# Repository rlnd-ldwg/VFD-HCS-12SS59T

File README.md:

# Arduino Driver for Samsung HCS-12SS59T VFDisplay
quick and simple schematics, driver and example

## 

## Code
-> source directory

## Schematics
### Display

- for simple DC filament supply  
  connect Vcc to VF+  
  mix normal and schottky diodes on VF- for desired voltage  
  keeping VF low extends tungsten filament lifetime  
  voltages starting with 2.7 V up to 3.6 V are working  
  do not exceed 125 mA!
- -> [AC Filament Supply](#ac-filament-supply) 

### Anode and Grid Supply

- activate Vdisp  
  in VFD.h set `SUPPLYMODE 0`
- the simple _VDON with 1N4148 does not switch off Vdisp entirely,  
  maybe it can be omitted because the 470 ohm resistor on Vdisp  
  restricts current for VFD grid and anode

### AC Filament Supply

- activate Vdisp  https://electronics.stackexchange.com/questions/230044/help-driving-a-vfd-display
  in VFD.h set `SUPPLYMODE 0`
- extended filament endurance  
  (-> google filament notching)
- better brightness distribution  
  (theoretical, can't see any difference to DC supply on this display)
- coil-less

### Combined Clocked Supply

- activate SUCLK_A/B  
  in VFD.h set `SUPPLYMODE 1`

## History
__V0.5__  
initial version  
__V0.6__  
AC filament supply  
__V0.7__  
AC filament supply _VDON  
__V0.8__  
AC filament supply polarity correction  
__V0.9__  
combined clocked supply

## Links
http://www.lapis-semi.com/en/data/datasheet-file_db/display/FEDL9289-01.pdf  
https://www.pollin.de/productdownloads/D121466D.PDF  
https://www.noritake-elec.com/technology/general-technical-information/vfd-operation  
http://www.kerrywong.com/2013/06/05/vfd-filament-driver-using-555/  
https://threeneurons.wordpress.com/vfd-stuff/
https://electronics.stackexchange.com/questions/230044/help-driving-a-vfd-display

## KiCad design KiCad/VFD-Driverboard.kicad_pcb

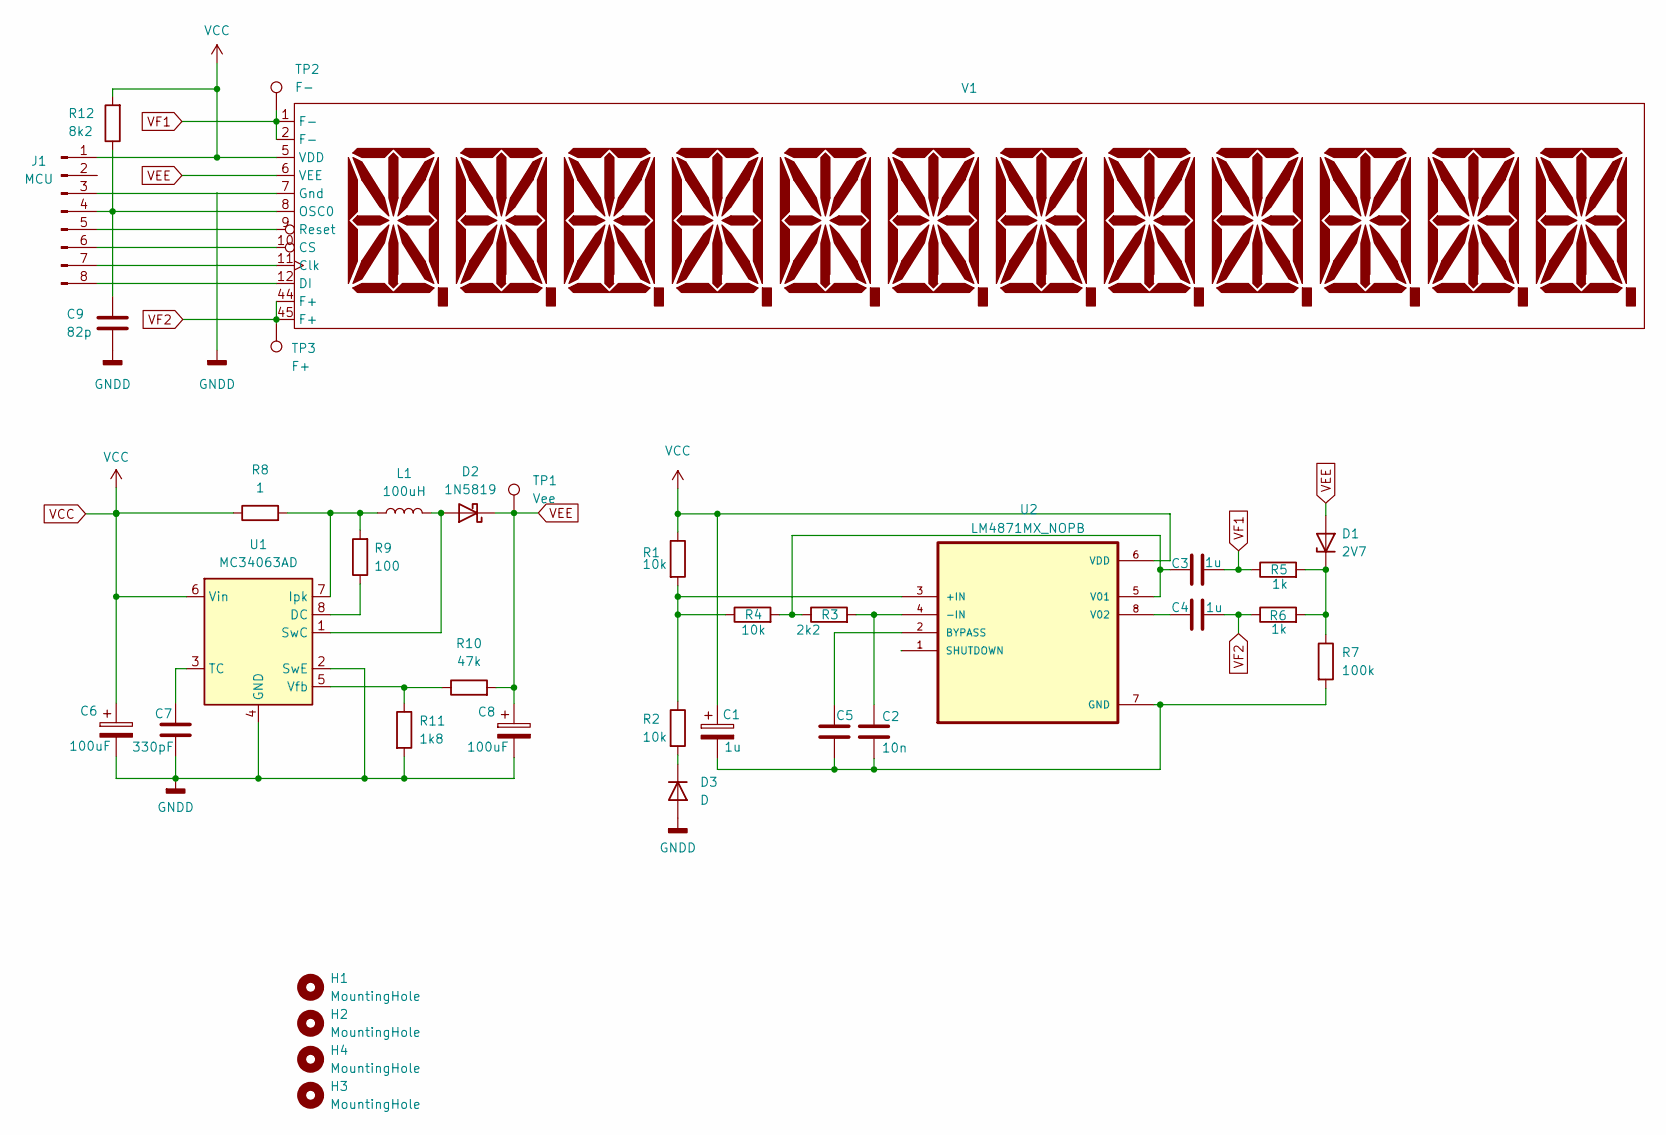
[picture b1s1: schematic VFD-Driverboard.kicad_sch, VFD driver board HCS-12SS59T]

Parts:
C1, C3, C4, C5: 1u; C_2220_5750Metric_Pad1.97x5.40mm_HandSolder
C2: 10n; C_1206_3216Metric_Pad1.33x1.80mm_HandSolder
C6, C8: 100uF; CP_EIA-7343-31_Kemet-D_Pad2.25x2.55mm_HandSolder
C7: 330pF; C_1206_3216Metric_Pad1.33x1.80mm_HandSolder
C9: 82p; C_1206_3216Metric_Pad1.33x1.80mm_HandSolder
D1: 2V7; D_2010_5025Metric_Pad1.52x2.65mm_HandSolder
D2: 1N5819; D_SOD-123
D3: D; D_2010_5025Metric_Pad1.52x2.65mm_HandSolder
H1, H2, H3, H4: MountingHole; MountingHole_3.2mm_M3_ISO14580_Pad_TopBottom
J1: MCU; PinSocket_1x08_P2.54mm_Vertical
L1: 100uH; IND_TAIYO_NRS8040_TAY
R1, R2, R4: 10k; R_1206_3216Metric_Pad1.30x1.75mm_HandSolder
R3: 2k2; R_1206_3216Metric_Pad1.30x1.75mm_HandSolder
R5, R6: 1k; R_1206_3216Metric_Pad1.30x1.75mm_HandSolder
R7: 100k; R_1206_3216Metric_Pad1.30x1.75mm_HandSolder
R8: 1; R_1206_3216Metric_Pad1.30x1.75mm_HandSolder
R9: 100; R_1206_3216Metric_Pad1.30x1.75mm_HandSolder
R10: 47k; R_1206_3216Metric_Pad1.30x1.75mm_HandSolder
R11: 1k8; R_1206_3216Metric_Pad1.30x1.75mm_HandSolder
R12: 8k2; R_1206_3216Metric_Pad1.30x1.75mm_HandSolder
TP1: Vee; TestPoint_Pad_D2.5mm
TP2: F-; TestPoint_Pad_D2.5mm
TP3: F+; TestPoint_Pad_D2.5mm
U1: MC34063AD; SOIC127P599X175-8N
U2: LM4871MX_NOPB; SOIC127P599X175-8N
V1: VFD HCS-12SS59T

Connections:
unnamed: D1.1 (K), R5.2, R6.2, R7.1
unnamed: D2.2 (A), L1.2, U1.1 (SwC)
unnamed: D3.1 (K), R2.2
unnamed: J1.3, V1.7 (Gnd)
unnamed: C9.2, J1.4, R12.1, V1.8 (OSC0)
unnamed: J1.5, V1.9 (Reset)
unnamed: J1.6, V1.10 (CS)
unnamed: J1.7, V1.11 (Clk)
unnamed: J1.8, V1.12 (DI)
unnamed: R9.1, U1.8 (DC)
unnamed: L1.1, R8.2, R9.2, U1.7 (Ipk)
unnamed: C7.1, U1.3 (TC)
unnamed: R10.1, R11.1, U1.5 (Vfb)
unnamed: R1.2, R2.1, R4.1, U2.3 (+IN)
unnamed: C2.1, R3.2, U2.4 (-IN)
unnamed: C5.1, U2.2 (BYPASS)
unnamed: C1.2, C2.2, C5.2, R7.2, U2.7 (GND)
unnamed: C3.1, R3.1, R4.2, U2.5 (V01)
unnamed: C4.1, U2.8 (V02)
VCC: C1.1, C6.1, J1.1, R1.1, R8.1, R12.2, U1.6 (Vin), U2.6 (VDD), V1.5 (VDD)
VEE: C8.1, D1.2 (A), D2.1 (K), R10.2, TP1.1, V1.6 (VEE)
VF1: C3.2, R5.1, TP2.1, V1.1 (F-), V1.2 (F-)
VF2: C4.2, R6.1, TP3.1, V1.44 (F+), V1.45 (F+)

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
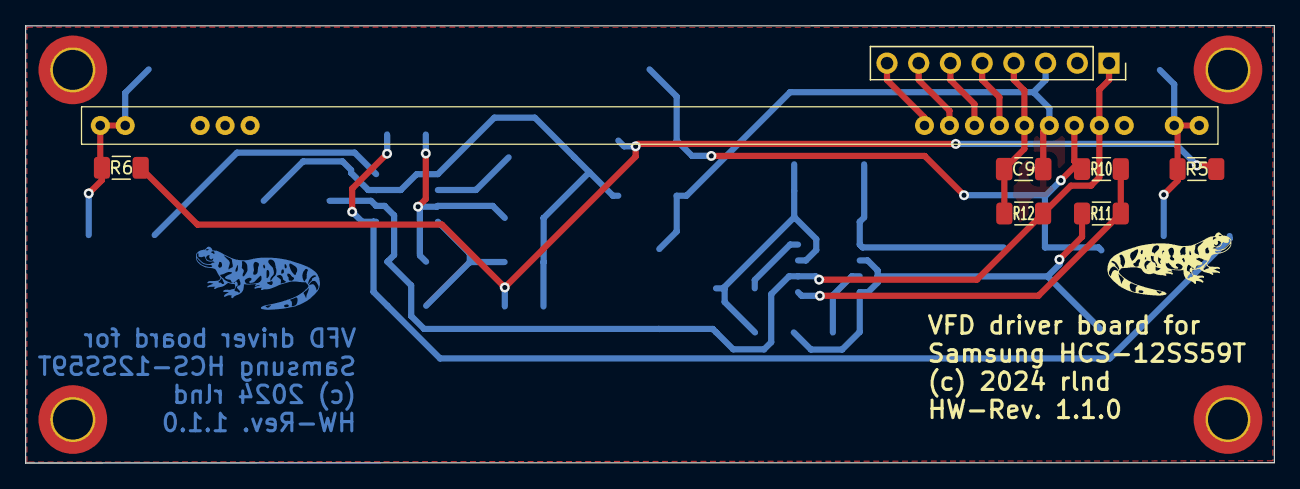
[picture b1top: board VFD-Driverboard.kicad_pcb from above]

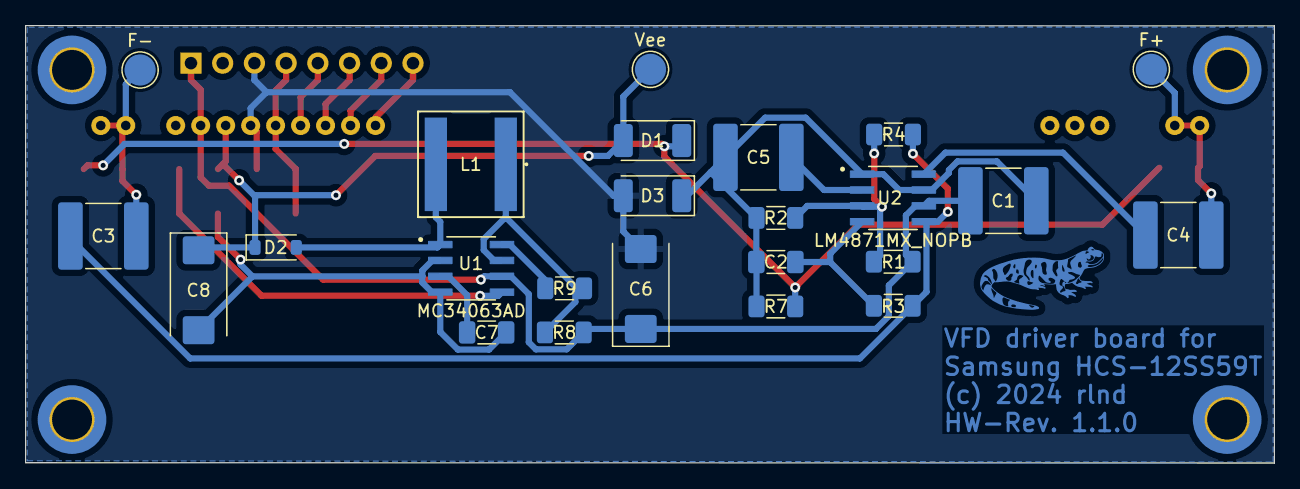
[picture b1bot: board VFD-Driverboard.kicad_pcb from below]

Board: 2 copper layers, 100.0 x 35.0 mm, 36 parts (24 on the bottom side), 25 nets.

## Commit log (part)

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2023-08-18 Schematic and board added
2024-02-05 Datasheets / Schematic, PCB
2024-02-05 KiCad Files
2024-02-16 KiCad schematic
2024-02-17 Schematic 1.0.6
2024-02-18 PCB & Gerber files
2024-02-21 Driverboard v. 1.0.4
2024-03-01 KiCad Directory renamed
2024-03-01 Removed old direktory
2024-07-08 SMD PCB
2024-07-08 PCB / tidy up
2024-07-08 new PCB
2024-07-08 tidy up
2024-07-21 added MPLAB project
2024-07-22 new vfd library
2024-07-22 cleanup
2024-07-23 new VFD routines
2024-07-23 changes SPI interface
2024-07-24 SPI routines
2024-07-25 spi/vfd interface
2024-07-25 Versions 0.2.0
2024-07-25 MPLAP temp files added

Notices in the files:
KiCad/VFD-Driverboard.kicad_pcb:
(c) 2024 rlnd
KiCad/VFD-Driverboard.kicad_sch:
© rlnd
